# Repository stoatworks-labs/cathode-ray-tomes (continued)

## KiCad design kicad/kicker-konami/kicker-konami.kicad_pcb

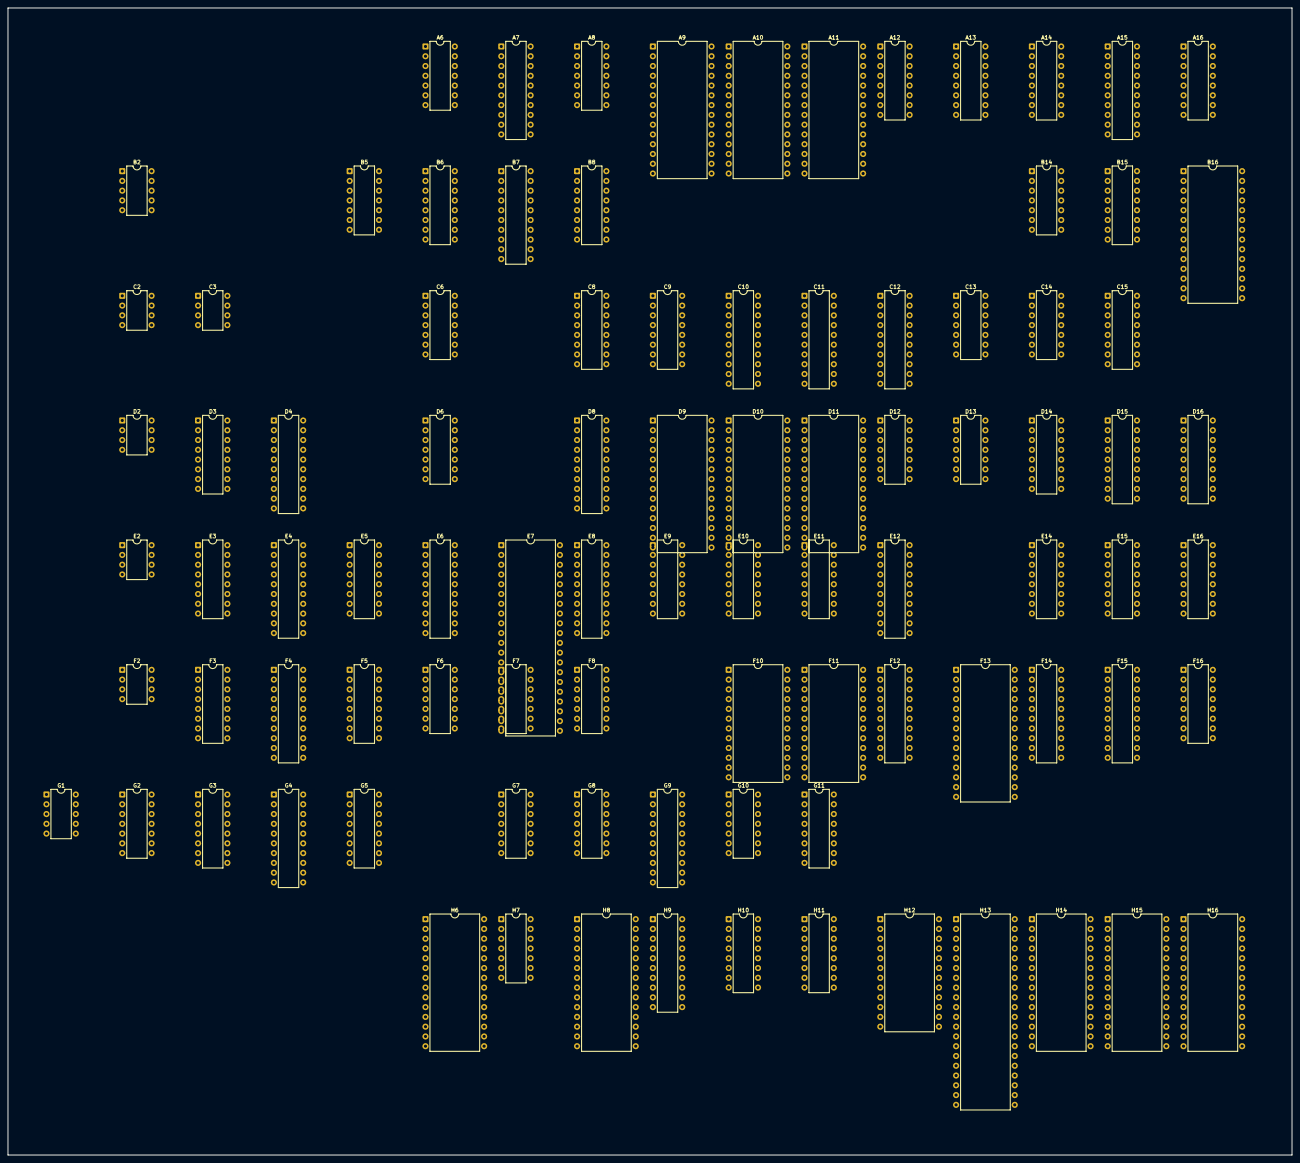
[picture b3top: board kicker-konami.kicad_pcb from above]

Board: 2 copper layers, 333.7 x 298.1 mm, 92 parts (0 on the bottom side), 423 nets, no tracks yet.

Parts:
A6: 74LS32; DIP-14_W7.62mm
A7, A15: 74LS273; DIP-20_W7.62mm
A8: 74LS86; DIP-14_W7.62mm
A9: KICKER_083; DIP-28_W15.24mm
A10, A11: 27128; DIP-28_W15.24mm
A12, A13, A14: TBP24S10N; DIP-16_W7.62mm
A16: 74LS157; DIP-16_W7.62mm
B2: LA4460; DIP-10_W7.62mm
B5: 74LS08; DIP-14_W7.62mm
B6, B15: 74LS174; DIP-16_W7.62mm
B7: 74LS377; DIP-20_W7.62mm
B8: TBP24S10N; DIP-16_W7.62mm
B14: 74LS32; DIP-14_W7.62mm
B16: KICKER_502; DIP-28_W15.24mm
C2, C3: KONAMI_005273; DIP-8_W7.62mm
C6: 74LS74; DIP-14_W7.62mm
C8, C9: 74LS138; DIP-16_W7.62mm
C10, C11: 74LS273; DIP-20_W7.62mm
C12: 74LS245; DIP-20_W7.62mm
C13: 74LS04; DIP-14_W7.62mm
C14: 74LS32; DIP-14_W7.62mm
C15: 74LS139; DIP-16_W7.62mm
D2: KONAMI_005273; DIP-8_W7.62mm
D3: 74LS253; DIP-16_W7.62mm
D4: 74LS273; DIP-20_W7.62mm
D6: 74LS14; DIP-14_W7.62mm
D8: 74LS244; DIP-20_W7.62mm
D9, D10, D11: 27128; DIP-28_W15.24mm
D12: 74LS32; DIP-14_W7.62mm
D13: 74LS08; DIP-14_W7.62mm
D14: 74LS163; DIP-16_W7.62mm
D15, D16: MBM2148; DIP-18_W7.62mm
E2: KONAMI_005273; DIP-8_W7.62mm
E3: 74LS253; DIP-16_W7.62mm
E4: 74LS273; DIP-20_W7.62mm
E5: SN76489AN; DIP-16_W7.62mm
E6, E12: 74LS245; DIP-20_W7.62mm
E7: MC6809E; DIP-40_W15.24mm
E8: 74LS244; DIP-20_W7.62mm
E9, E10, E11: 74LS157; DIP-16_W7.62mm
E14, E15, E16: 74LS163; DIP-16_W7.62mm
F2: KONAMI_005273; DIP-8_W7.62mm
F3: 74LS253; DIP-16_W7.62mm
F4, F15: 74LS273; DIP-20_W7.62mm
F5: SN76489AN; DIP-16_W7.62mm
F6, F7: 74LS74; DIP-14_W7.62mm
F8: 74LS08; DIP-14_W7.62mm
F10, F11: TMM2009P-A; DIP-24_W15.24mm
F12: 74LS245; DIP-20_W7.62mm
F13: KONAMI_085; DIP-28_W15.24mm
F14: 74LS377; DIP-20_W7.62mm
F16: TBP24S10N; DIP-16_W7.62mm
G1: TA7900S; DIP-10_W7.62mm
G2: 74LS07; DIP-14_W7.62mm
G3: 74LS253; DIP-16_W7.62mm
G4: 74LS244; DIP-20_W7.62mm
G5: 74LS367; DIP-16_W7.62mm
G7: 74LS04; DIP-14_W7.62mm
G8, G10: 74LS86; DIP-14_W7.62mm
G9: 74LS273; DIP-20_W7.62mm
G11: 74LS157; DIP-16_W7.62mm
H6: KONAMI_504; DIP-28_W15.24mm
H7: 74LS74; DIP-14_W7.62mm
H8: KONAMI_082; DIP-28_W15.24mm
H9: 74LS244; DIP-20_W7.62mm
H10, H11: 74LS157; DIP-16_W7.62mm
H12: RAM_2016; DIP-24_W15.24mm
H13: KONAMI_503; DIP-40_W15.24mm
H14, H15: 27128; DIP-28_W15.24mm
H16: KICKER_083; DIP-28_W15.24mm

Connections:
+12V: A10.14, A10.20, A10.22, A11.14, A11.20, A11.22, A12.13, A12.14, A13.13, A13.14, A14.13, A14.14, B8.13, B8.14, B14.5, D3.8, D8.1, D8.10, D8.19, D9.14, D9.20, D10.14, D10.20, D11.14, D11.20, D15.9, D15.15, D15.16, D16.9, D16.15, D16.16, E3.8, E6.19, E7.1, E7.39, E8.1, E8.10, E8.19, E9.2, E9.5, E9.11, E9.14, E9.15, E10.15, E11.11, E11.15, F3.8, F7.2, F7.12, F10.12, F11.12, F16.13, F16.14, G1.1, G1.2, G1.5, G3.8, G4.10, G5.15, G8.5, G11.15, H6.14, H8.27, H9.10, H10.14, H10.15, H11.15, H12.18, H13.20, H14.14, H14.20, H14.22, H15.14, H15.20, H15.22
/1P_DOWN: F2.7, F3.5
/1P_LEFT: E2.5, G3.11
/1P_RIGHT: E2.3, G3.5
/1P_SHOOT1: D2.7, E3.11
/1P_SHOOT2: D2.3, E3.5
/1P_START: C2.7, F3.6
/1P_UP: E2.7, F3.11
/2P_LEFT: C2.3, G3.12
/2P_RIGHT: C2.5, G3.4
/2P_SHOOT1: C3.1, E3.12
/2P_SHOOT2: C2.1, E3.4
/2P_START: D2.1, E3.10
/2P_UP: D2.5, F3.12
/A0: D8.11, E7.8
/A1: D8.8, E7.9
/A2: D8.13, E7.10
/A3: D8.6, E7.11
/A4: D8.15, E7.12
/A5: D8.4, E7.13
/A6: D8.17, E7.14
/A7: D8.2, E7.15
/A8: E7.16, E8.2
/A9: E7.17, E8.17
/A10: E7.18, E8.4
/A11: E7.19, E8.6
/A12: E7.20, E8.8
/A13: E7.21, E8.11
/A14: E7.22, E8.13
/A15: E7.23, E8.15
/AD0: D3.14, D8.9, D9.10, D10.10, D11.10, E3.14, E11.3, F3.14, G3.14, H11.3
/AD1: D3.2, D8.12, D9.9, D10.9, D11.9, E3.2, E11.6, F3.2, G3.2, H11.10
/AD2: D8.7, D9.8, D10.8, D11.8, E10.3, H11.6
/AD3: D8.14, D9.7, D10.7, D11.7, E10.13, H11.13
/AD4: D8.5, D9.6, D10.6, D11.6, E10.6, G11.10
/AD5: D8.16, D9.5, D10.5, D11.5, E10.10, G11.6
/AD6: D8.3, D9.4, D10.4, D11.4, E9.6, G11.13
/AD7: D8.18, D9.3, D10.3, D11.3, E9.10, G11.3
/AD8: C9.1, D9.25, D10.25, D11.25, E8.18, E9.3, H10.10
/AD9: C9.2, D9.24, D10.24, D11.24, E8.3, E9.13, H10.6
/AD10: C9.3, D9.21, D10.21, D11.21, E8.16, H10.3
/AD11: C8.1, D9.23, D10.23, D11.23, E8.14
/AD12: C8.2, D9.2, D10.2, D11.2, E8.12
/AD13: C8.3, D9.26, D10.26, D11.26, E8.9
/AD14: C15.13, E8.7
/AD15: C15.14, E8.5
/AFE: C9.14, G2.5
/CHAR0: A9.3, A11.16
/CHAR1: A9.4, A11.11
/CHAR2: A9.5, A10.16
/CHAR3: A9.6, A10.11
/CHAR4: A9.7, A11.17
/CHAR5: A9.8, A11.12
/CHAR6: A9.9, A10.17
/CHAR7: A9.10, A10.12
/CHAR8: A9.25, A11.13
/CHAR9: A9.26, A11.18
/CHAR10: A9.24, A10.18
/CHAR11: A9.20, A10.19
/CHAR12: A9.22, A11.19
/CHAR13: A9.21, A11.15
/CHAR14: A9.23, A10.13
/CHAR15: A9.19, A10.15
/CLK1: B6.9, B16.5, C6.3, G7.8
/CLK2: A9.1, B7.11, F6.3, F6.11, G7.6, G9.11
/CLK2A: A15.11, B14.4, C6.11, F14.11, G7.2, H16.1
/CLK2B: D14.2, D15.10, D16.10, E14.2, E15.2, E16.2, G7.4
/CNTCLR: B16.27, H7.5, H8.1
/COIN1: D4.5, G2.1
/COIN2: D4.15, G2.3
/COIN_1: F2.5, G3.10
/COIN_2: F2.3, G3.6
/COLOR: B15.9, C8.12
/CRA0: A8.8, A10.10, A11.10
/CRA1: A8.6, A10.9, A11.9
/CRA2: A8.11, A10.8, A11.8
/CRA3: A8.3, A10.7, A11.7
/CRA4: A10.6, A11.6, C11.2
/CRA5: A10.5, A11.5, C11.19
/CRA6: A10.4, A11.4, C11.5
/CRA7: A10.3, A11.3, C11.16
/CRA8: A10.25, A11.25, C11.6
/CRA9: A10.24, A11.24, C11.15
/CRA10: A10.21, A11.21, C11.9
/CRA11: A10.23, A11.23, C11.12
/CRA12: A7.9, A10.2, A11.2
/CRA13: A7.15, A10.26, A11.26
/DB0: B15.14, C12.18, D4.18, D9.11, D10.11, D11.11, E4.13, E6.2, E12.11, F4.13, F12.18, F13.1, G3.9, G4.12, G5.9
/DB1: B15.13, C12.17, D4.3, D9.12, D10.12, D11.12, E4.8, E6.3, E12.12, F4.8, F12.17, F13.2, G3.7, G4.9, G5.7
/DB2: B15.3, C12.16, D4.17, D9.13, D10.13, D11.13, E4.14, E6.4, E12.13, F3.9, F4.14, F12.16, F13.3, G4.14, G5.5
/DB3: C12.15, D4.4, D9.15, D10.15, D11.15, E4.7, E6.5, E12.14, F3.7, F4.7, F12.15, F13.4, G4.7, G5.3
/DB4: C12.14, D4.14, D9.18, D10.18, D11.18, E3.9, E4.18, E6.8, E12.17, F4.18, F12.12, F13.5, G4.16
/DB5: C12.13, D4.7, D9.17, D10.17, D11.17, E3.7, E4.3, E6.7, E12.16, F4.3, F12.13, F13.6, G4.5
/DB6: C12.12, D3.9, D4.13, D9.16, D10.16, D11.16, E4.4, E6.6, E12.15, F4.4, F12.14, F13.7, G4.18
/DB7: C12.11, D3.7, D4.8, D9.19, D10.19, D11.19, E4.17, E6.9, E12.18, F4.17, F12.11, F13.8, G4.3
/DV0: C10.3, C11.3, C12.2, H12.9
/DV1: C10.18, C11.18, C12.3, H12.10
/DV2: C10.4, C11.4, C12.4, H12.11
/DV3: C10.17, C11.17, C12.5, H12.13
/DV4: C10.7, C11.7, C12.6, H12.14
/DV5: C10.14, C11.14, C12.7, H12.15
/DV6: C10.8, C11.8, C12.8, H12.16
/DV7: C10.13, C11.13, C12.9, H12.17
/EXTRA1: C3.3, E3.6
/EXTRA2: C3.5, D3.10
/EXTRA3: C3.7, D3.11
/FLIP: C13.3, D4.19, F13.13, G8.4
/H1: B6.13, E5.14, G9.2, H6.10, H7.12
/H2: B6.6, B16.7, D6.5, F5.14, G9.19
/H4: B6.11, C10.11, E11.2, G8.10, G9.5, H10.2
/H8: B6.3, G8.13, G9.16
/H16: E11.5, G9.6, G10.2
/H32: E10.2, F13.9, G9.15, G10.13
/H64: E10.14, F13.12, G9.9, G10.9
/H128: B5.1, G9.12, G10.5
/H256: B6.15, B16.9, E10.11
/HF8: G8.11, H11.2
/HF16: B14.12, G10.8, H11.11
/HF32: B14.13, G10.11, H11.5
/HF64: G10.3, H11.14
/HF128: B14.9, G10.6, G11.11
/HH1: B5.13, B6.12
/HH2: B6.7, H6.11
/HH4: B6.10, G8.1, H6.12, H13.16
/HH8: B6.2, H6.13, H13.17
/HH256: C6.5, F13.16
/IN5: C9.10, G4.1, G4.19
/IN6: C9.9, G5.1
/INTSHOW: C9.13, F13.11
/IOEN: C9.7, D3.1, D3.15, E3.1, E3.15, F3.1, F3.15, G3.1, G3.15
/IOW: A6.5, C9.15
/IRQ: D4.16, F7.10
/LD: A9.27, C13.2, H16.27
/NMI: D4.2, F7.4
/OBJ0: A16.14, B16.18
/OBJ1: A16.3, B16.17
/OBJ2: A16.11, B16.16
/OBJ3: A16.2, B16.15
/OBJCOL0: F16.5, H16.16
/OBJCOL1: F16.6, H16.13
/OBJCOL2: F16.7, H16.17
/OBJCOL3: F16.4, H16.12
/OBJCS1: C8.9, D12.1, D12.4, E12.19
/OBJCS2: C8.10, D12.9, D12.13, F12.19
/OBJNEW0: B16.10, F16.12
/OBJNEW1: B16.11, F16.11
/OBJNEW2: B16.12, F16.10
/OBJNEW3: B16.13, F16.9
/OBJPAL0: F14.16, F16.3
/OBJPAL1: F14.5, F16.2
/OBJPAL2: F14.19, F16.1
/OBJPAL3: F14.2, F16.15
/OD0: E12.9, E15.3, E16.3, F10.9, F15.4
/OD1: E12.8, E15.4, E16.4, F10.10, F15.7
/OD2: E12.7, E15.5, E16.5, F10.11, F15.14
/OD3: E12.6, E15.6, E16.6, F10.13, F15.17
/OD4: D14.3, E12.5, E14.3, F10.14, F15.3
/OD5: D14.4, E12.4, E14.4, F10.15, F15.18
/OD6: D14.5, E12.3, E14.5, F10.16, F15.8
/OD7: D14.6, E12.2, E14.6, F10.17, F15.13
/OR0: E11.4, F10.8, F11.8
/OR1: E11.7, F10.7, F11.7
/OR2: E10.4, F10.6, F11.6
/OR3: E10.12, F10.5, F11.5
/OR4: E10.7, F10.4, F11.4
/OR5: E10.9, F10.3, F11.3
/OR6: E9.7, F10.2, F11.2
/OR7: E9.9, F10.1, F11.1
/OR8: E9.4, F10.23, F11.23
/OR9: E9.12, F10.22, F11.22
/PAL0: A12.5, A13.5, A14.5, A15.6
/PAL1: A12.6, A13.6, A14.6, A15.12
/PAL2: A12.7, A13.7, A14.7, A15.9
/PAL3: A12.4, A13.4, A14.4, A15.15
/PAL4: A12.3, A13.3, A14.3, A15.5
/PAL5: A12.2, A13.2, A14.2, A15.16
/PAL6: A12.1, A13.1, A14.1, A15.19
/PAL7: A12.15, A13.15, A14.15, A15.2
/RC_SERVICE: E2.1, F3.10
/R~WB: C12.1, D6.1, E12.1, F12.1, G5.13, H6.6
/R~W: E6.1, E7.32, G5.14
/R~WBB: D6.2, E11.10, H10.13
/R~WV: A6.4, A6.10, D12.5, D12.10, H6.22
/SCR0: A16.13, B8.12
/SCR1: A16.6, B8.11
/SCR2: A16.10, B8.10
/SCR3: A16.5, B8.9
/SD0: F11.9, F12.2, F14.17, H13.8
/SD1: F11.10, F12.3, F14.4, H13.7
/SD2: F11.11, F12.4, F14.18, H13.6
/SD3: F11.13, F12.5, F14.3, H13.5
/SD4: F11.14, F12.6, H13.4
/SD5: F11.15, F12.7, H13.3
/SD6: F11.16, F12.8, H13.2
/SD7: F11.17, F12.9, H13.1
/SE: C13.9, F6.12, H6.3
/SQ: F6.2, H6.25
/TI1D0: E4.12, E5.10
/TI1D1: E4.9, E5.11
/TI1D2: E4.15, E5.12
/TI1D3: E4.6, E5.13
/TI1D4: E4.19, E5.15
/TI1D5: E4.2, E5.1
/TI1D6: E4.5, E5.2
/TI1D7: E4.16, E5.3
/TI2D0: F4.12, F5.10
/TI2D1: F4.9, F5.11
/TI2D2: F4.15, F5.12
/TI2D3: F4.6, F5.13
/TI2D4: F4.19, F5.15
/TI2D5: F4.2, F5.1
/TI2D6: F4.5, F5.2
/TI2D7: F4.16, F5.3
/TIDATA1: C8.13, E4.11
/TIDATA2: C8.14, F4.11
/TITG1: C9.11, F8.1
/TITG2: C9.12, F8.10
/V1: A7.7, H8.26, H9.2, H13.32
/V2: A7.17, H8.25, H9.17, H13.33
/V4: A7.4, H8.24, H9.4, H13.34
/V8: H8.23, H9.15, H13.35
/V16: F7.3, H8.22, H9.6, H13.36
/V32: H8.21, H9.13, H13.37
/V64: H8.20, H9.8, H13.38
/V128: H8.19, H9.11, H13.39
/VBLANK: F7.11, H8.16
/VD0: H14.16, H16.3
/VD1: H14.11, H16.4
/VD2: H15.16, H16.5
/VD3: H15.11, H16.6
/VD4: H14.17, H16.7
/VD5: H14.12, H16.8
/VD6: H15.17, H16.9
/VD7: H15.12, H16.10
/VD8: H14.18, H16.25
/VD9: H14.13, H16.26
/VD10: H15.18, H16.24
/VD11: H15.13, H16.20
/VD12: H14.19, H16.22
/VD13: H14.15, H16.21
/VD14: H15.19, H16.23
/VD15: H15.15, H16.19
/VGAP: C8.11, F13.15
/VSCR0: F13.27, H9.18
/VSCR1: F13.26, H9.3
/VSCR2: F13.25, H9.16
/VSCR3: F13.24, G11.5, H9.5
/VSCR4: F13.23, G11.14, H9.14
/VSCR5: F13.22, G11.2, H9.7
/VSCR6: F13.21, H9.12, H10.11
/VSCR7: F13.20, H9.9, H10.5
/hflip: A6.1, A7.2, A8.2
/prehflip: A7.3, C10.6
/prevflip: A7.18, C10.15
/tile_pal0: B7.17, C10.2
/tile_pal1: B7.4, C10.19
/tile_pal2: B7.3, C10.5
/tile_pal3: B7.18, C10.16
/vflip: A7.19, A8.5, A8.10, A8.13
/~CLK1: G7.9, H6.26, H7.11
/~COMPBLANK: A16.15, H6.17
/~EE: D6.13, F6.9
/~E: B5.4, C13.8, H7.3
/~H2: C8.6, C9.6, C14.1, D6.6, E9.1, E10.1, E11.1, G11.1, H10.1, H11.1
/~H4: A8.1, G8.8
/~H256B: B5.2, B6.14, C6.9, H6.8
/~H256: C6.12, H8.10
/~HH256: C6.6, H9.1, H9.19
/~IRQ: E7.3, F7.9
/~LDOUT: A7.11, B16.8, C11.11, H6.21
/~LD: A6.2, C13.1, C15.1, H6.20, H13.15
/~NMI: E7.2, F7.5
/~OBJ_SEL: A15.4, A16.1, B16.19
/~Q: B5.5, D6.9, F6.5
/~RESET: D4.1, E7.37, G1.7, H7.1
/~VRAMCS: A6.9, C8.7, C12.19
GND: A12.16, A13.16, A14.16, B8.16, F16.16
unnamed: A7.8, C10.9
unnamed: A7.14, C10.12
unnamed: A7.5, A8.12
unnamed: A7.6, A8.9
unnamed: A7.16, A8.4
unnamed: A9.16, B8.5
unnamed: A9.13, B8.6
unnamed: A9.17, B8.7
unnamed: A9.12, B8.4
unnamed: A9.2, B7.6
unnamed: A15.3, B15.2
unnamed: A15.7, A16.12
unnamed: A15.8, A16.9
unnamed: A15.13, A16.7
unnamed: A15.14, A16.4
unnamed: A15.17, B15.15
unnamed: A15.18, B15.12
unnamed: B5.11, C14.2, D12.2, D12.12
unnamed: B7.7, G8.3
unnamed: B7.2, B8.1
unnamed: B7.5, B8.2
unnamed: B7.16, B8.3
unnamed: B7.19, B8.15
unnamed: A6.3, B7.1
unnamed: B14.10, B14.11
unnamed: B16.1, D16.14
unnamed: B16.2, D16.13
unnamed: B16.3, D16.12
unnamed: B16.4, D16.11
unnamed: B16.26, D15.14
unnamed: B16.25, D15.13
unnamed: B16.24, D15.12
unnamed: B16.23, D15.11
unnamed: B14.6, B16.6
unnamed: B16.22, C13.11, C14.4, C15.3
unnamed: B16.21, C15.2
unnamed: B16.20, C13.5, D13.9
unnamed: C6.2, C6.8
unnamed: C8.15, C9.4, C9.5
unnamed: C13.4, G8.2
unnamed: C13.6, D13.1
unnamed: C13.10, C14.9
unnamed: C14.3, D13.5, D13.13
unnamed: C15.6, E14.1, E15.1
unnamed: C15.7, D14.1, E16.1
unnamed: B5.6, C15.15
unnamed: C8.4, C8.5, C15.12
unnamed: C15.11, D9.22
unnamed: C15.10, D10.22
unnamed: C15.9, D11.22
unnamed: A6.6, D4.11
unnamed: D6.3, G2.6
unnamed: D12.3, D13.12
unnamed: D12.11, D13.4
unnamed: D14.7, D14.10, E16.15
unnamed: D14.14, D16.3
unnamed: D14.13, D16.2
unnamed: D14.12, D16.1
unnamed: D14.11, D16.17
unnamed: C14.6, D14.9, E16.9
unnamed: D15.5, E15.14
unnamed: D15.6, E15.13
unnamed: D15.7, E15.12
unnamed: D15.4, E15.11
unnamed: D15.3, E14.14
unnamed: D15.2, E14.13
unnamed: D15.1, E14.12
unnamed: D15.17, E14.11
unnamed: D13.3, D15.8
unnamed: D16.5, E16.14
unnamed: D16.6, E16.13
unnamed: D16.7, E16.12
unnamed: D16.4, E16.11
unnamed: D13.8, D16.8
unnamed: E5.4, E5.5, F8.2
unnamed: E5.6, F8.3
unnamed: E6.18, E7.31
unnamed: E6.17, E7.30
unnamed: E6.16, E7.29
unnamed: E6.15, E7.28
unnamed: E6.14, E7.27
unnamed: E6.13, E7.26
unnamed: E6.12, E7.25
unnamed: E6.11, E7.24
unnamed: D6.12, E7.34
unnamed: D6.8, E7.35
unnamed: B5.3, E10.5
unnamed: E11.9, F10.20, F11.20
unnamed: E14.7, E14.10, E15.15
unnamed: C14.8, E14.9, E15.9
unnamed: F5.4, F5.5, F8.9
unnamed: F5.6, F8.8
unnamed: D13.11, F10.18
unnamed: D12.6, F10.21
unnamed: D13.6, F11.18
unnamed: D12.8, F11.21
unnamed: B14.8, F13.10
unnamed: F14.7, H13.29
unnamed: F14.8, H13.30
unnamed: D13.2, D13.10, F14.6
unnamed: F14.9, H16.2
unnamed: C14.5, C14.10, F14.1, H13.18
unnamed: F15.11, H13.19
unnamed: F15.2, H14.21, H15.21
unnamed: F15.5, H14.4, H15.4
unnamed: F15.6, H14.3, H15.3
unnamed: F15.9, H14.2, H15.2
unnamed: F15.12, H14.26, H15.26
unnamed: F15.15, H14.25, H15.25
unnamed: F15.16, H14.24, H15.24
unnamed: F15.19, H14.23, H15.23
unnamed: D6.4, G1.9
unnamed: G5.12, H8.17
unnamed: G9.3, H8.2
unnamed: G9.4, H8.4
unnamed: G9.7, H8.6
unnamed: G9.8, H8.8
unnamed: G9.13, H8.9
unnamed: G9.14, H8.7
unnamed: G9.17, H8.5
unnamed: G9.18, H8.3
unnamed: G8.6, G8.9, G8.12, G10.1, G10.4, G10.10, G10.12
unnamed: G11.4, H12.1
unnamed: G11.7, H12.3
unnamed: G11.12, H12.2
unnamed: G11.9, H12.4
unnamed: G7.1, G7.3, G7.5, G7.13, H6.2
unnamed: H6.9, H8.15
unnamed: B5.12, H7.9
unnamed: G7.12, H8.13
unnamed: H10.4, H12.19
unnamed: H10.7, H12.22
unnamed: H10.12, H12.20
unnamed: H10.9, H12.23
unnamed: H11.4, H12.8
unnamed: H11.7, H12.6
unnamed: H11.12, H12.5
unnamed: H11.9, H12.7
unnamed: A6.8, H12.21
unnamed: H13.11, H14.7, H15.7
unnamed: H13.10, H14.6, H15.6
unnamed: H13.14, H14.10, H15.10
unnamed: H13.13, H14.9, H15.9
unnamed: H13.12, H14.8, H15.8
unnamed: H13.9, H14.5, H15.5
VCC: A7.1, A10.1, A10.27, A10.28, A11.1, A11.27, A11.28, A12.8, A13.8, A14.8, A15.1, B6.1, B8.8, B15.1, C6.1, C6.4, C6.10, C6.13, C10.1, C11.1, D3.16, D8.20, D9.1, D9.27, D9.28, D10.1, D10.27, D10.28, D11.1, D11.27, D11.28, D15.18, D16.18, E3.16, E4.1, E7.7, E8.20, E15.7, E15.10, E16.7, E16.10, F3.16, F4.1, F6.1, F6.4, F6.10, F6.13, F7.1, F7.13, F10.19, F10.24, F11.19, F11.24, F15.1, F16.8, G1.4, G3.16, G4.20, G9.1, H6.27, H6.28, H7.2, H7.4, H7.10, H7.13, H8.12, H9.20, H13.40, H14.1, H14.27, H14.28, H15.1, H15.27, H15.28

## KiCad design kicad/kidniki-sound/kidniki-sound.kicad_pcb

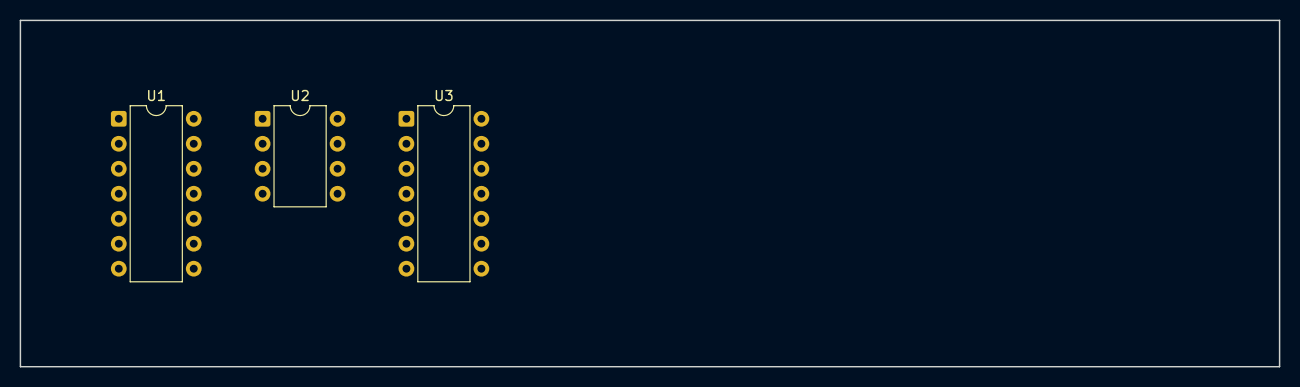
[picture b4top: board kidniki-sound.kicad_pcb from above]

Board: 2 copper layers, 128.0 x 35.2 mm, 3 parts (0 on the bottom side), 6 nets, no tracks yet.

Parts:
U1: LM324; DIP-14_W7.62mm
U2: LM358; DIP-8_W7.62mm
U3: MC14584B; DIP-14_W7.62mm

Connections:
+5V: U1.4, U2.8, U3.14
GND: U1.11, U2.4, U3.7
unnamed: U1.8, U1.9
unnamed: U2.6, U2.7
unnamed: U1.1, U1.2
unnamed: U2.1, U2.2

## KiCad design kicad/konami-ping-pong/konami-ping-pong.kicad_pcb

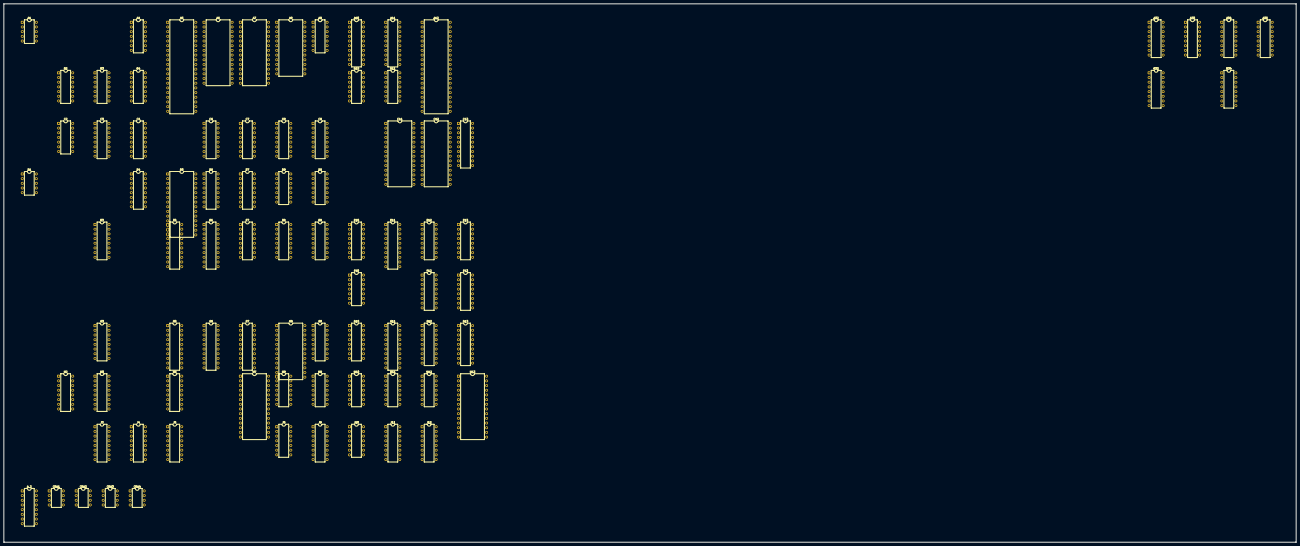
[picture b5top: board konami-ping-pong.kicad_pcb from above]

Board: 2 copper layers, 700.4 x 291.8 mm, 84 parts (0 on the bottom side), 361 nets, no tracks yet.

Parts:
A1: TA7900S; DIP-10_W7.62mm
A4: 74LS74; DIP-14_W7.62mm
A5: Z80CPU; DIP-40_W15.24mm
A6, A7: 27128; DIP-28_W15.24mm
A8: HM6116P-3; DIP-24_W15.24mm
A9: 74LS10; DIP-14_W7.62mm
A10: 74LS245; DIP-20_W7.62mm
A11: 74LS374; DIP-20_W7.62mm
A12: KONAMI_503; DIP-40_W15.24mm
A32, A34: 74LS194; DIP-16_W7.62mm
A33, A35: 74LS157; DIP-16_W7.62mm
A_2: 74LS368; DIP-16_W7.62mm
B2: 74LS07; DIP-14_W7.62mm
B3: 74LS107; DIP-14_W7.62mm
B4: 74xx74; DIP-14_W7.62mm
B10: 7400; DIP-14_W7.62mm
B11: 74xx86; DIP-14_W7.62mm
B32, B34: 74LS194; DIP-16_W7.62mm
C2: 74xx04; DIP-14_W7.62mm
C3: 74LS138; DIP-16_W7.62mm
C4: 74LS174; DIP-16_W7.62mm
C6: 74LS161; DIP-16_W7.62mm
C7, C8, C9: 74LS157; DIP-16_W7.62mm
C11: 27128; DIP-28_W15.24mm
C12: 2764; DIP-28_W15.24mm
C13: 74LS273; DIP-20_W7.62mm
CRA1: 005273X4; DIP-8_W7.62mm
CRA2, CRA3, CRA4: KONAMI_005273; DIP-8_W7.62mm
D1: LA4460; DIP-10_W7.62mm
D4: SN76489AN; DIP-16_W7.62mm
D5: KONAMI_UK; DIP-28_W15.24mm
D6: 74LS161; DIP-16_W7.62mm
D7: 74LS139; DIP-16_W7.62mm
D8: 74LS32; DIP-14_W7.62mm
D9: 74LS00; DIP-14_W7.62mm
E3: 74LS253; DIP-16_W7.62mm
E5, E11: 74LS273; DIP-20_W7.62mm
E6: 74LS245; DIP-20_W7.62mm
E7, E8, E9: 74LS157; DIP-16_W7.62mm
E10: 74LS367; DIP-16_W7.62mm
E12, E13: 74LS163; DIP-16_W7.62mm
F10: 74LS14; DIP-14_W7.62mm
F12, F13: 74LS163; DIP-16_W7.62mm
G3: 74LS253; DIP-16_W7.62mm
G5, G11: 74LS377; DIP-20_W7.62mm
G6, G7: 74LS273; DIP-20_W7.62mm
G8: HM6116P-3; DIP-24_W15.24mm
G9, G10: 74LS161; DIP-16_W7.62mm
G12, G13: MBM2148; DIP-18_W7.62mm
H2, H3: 74LS253; DIP-16_W7.62mm
H5: TBP24S10N; DIP-16_W7.62mm
H7: 2764; DIP-28_W15.24mm
H8, H11: 74LS08; DIP-14_W7.62mm
H9: 74LS74; DIP-14_W7.62mm
H10: 74xx04; DIP-14_W7.62mm
H12: 74LS32; DIP-14_W7.62mm
H13: kicker_502; DIP-28_W15.24mm
J3: TBP18S030; DIP-16_W7.62mm
J4, J9: 74LS174; DIP-16_W7.62mm
J5: 74LS157; DIP-16_W7.62mm
J8: 74LS86; DIP-14_W7.62mm
J10: 74LS74; DIP-14_W7.62mm
J11: TBP24S10N; DIP-16_W7.62mm
J12: 74LS139; DIP-16_W7.62mm

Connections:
/1V: A12.32, G10.7, G10.10, J9.14, J10.9
/2V: A12.33, G10.14, J9.6
/4V: A12.34, G10.13, J9.4
/8V: A12.35, E8.11, G10.12
/16V: A4.11, A12.36, B4.11, E8.5, G10.11
/32V: A9.5, A12.37, E8.14, G9.14
/64V: A9.4, A12.38, E9.14, G9.13
/128V: A9.3, A12.39, E9.2, G9.12
/256V: G9.11, H11.4
/BLANKING: D9.8, J5.15
/CLK6M: A_2.13, D5.11, H13.5
/CPUSEL: C2.2, C7.1, C8.1, C9.1, E7.1, E8.1, E9.1, H8.10
/DB0: A10.11, C4.11, D5.8, E5.14, E6.14, H2.9
/DB1: A10.12, C4.13, D5.7, E5.7, E6.13, H2.7
/DB2: A10.13, C4.4, D5.6, E5.4, E6.16, H3.9
/DB3: A10.14, C4.6, D5.5, E5.17, E6.15, H3.7
/DB4: A10.15, C4.3, D5.4, E3.9, E5.3, E6.18
/DB5: A10.16, C4.14, D5.3, E3.7, E5.18, E6.17
/DB6: A10.17, D5.2, E5.8, E6.11, G3.9
/DB7: A10.18, D5.1, E5.13, E6.12, G3.7
/H1: A4.5, A9.1, A_2.12, B10.1, C6.7, C6.10, D4.14, D5.10
/H2: A9.13, B10.2, C6.14, H13.7
/H4: A9.2, B11.1, C2.13, C6.13, E9.5, G6.11, J8.13
/H4': A12.16, B11.6, C7.5, J12.2
/H8: A12.17, B11.13, C6.12, C7.14, E7.2
/H8'': A11.1, H10.10
/H8´: B11.8, J12.3
/H16: C6.11, C7.2, E7.11, J10.3
/H32: C7.11, D6.14, D9.12, E7.5
/H64: C8.5, D6.13, E7.14, F10.1
/H128: D6.12, E8.2, H8.12
/H256: D6.11, H8.13, H10.5, H12.1
/H256´: H9.12, H12.3, H13.9
/LD_A: A33.6, A33.11, A35.6, A35.11, D9.4, H10.12
/MAINA0: A5.30, A6.10, A7.10, C7.6, E7.3
/MAINA1: A5.31, A6.9, A7.9, C7.13, E7.10
/MAINA2: A5.32, A6.8, A7.8, C7.3, E7.6
/MAINA3: A5.33, A6.7, A7.7, C7.10, E7.13
/MAINA4: A5.34, A6.6, A7.6, C8.6, E8.3
/MAINA5: A5.35, A6.5, A7.5, C8.13, E8.10
/MAINA6: A5.36, A6.4, A7.4, C8.3, E8.6
/MAINA7: A5.37, A6.3, A7.3, C8.10, E8.13, E10.14
/MAINA8: A5.38, A6.25, A7.25, C9.10, E9.13, E10.12
/MAINA9: A5.39, A6.24, A7.24, C3.1, C9.6, E9.3
/MAINA10: A5.40, A6.21, A7.21, C3.2, C9.3, E9.6
/MAINAB7: E3.14, E10.13, G3.14, H2.14, H3.14
/MAINAB8: E3.2, E10.11, G3.2, H2.2, H3.2
/MAIN_DCDR: D7.10, D8.4, H10.3
/OC0: H13.18, J5.2
/OC1: H13.17, J5.5
/OC2: H13.16, J5.11
/OC3: H13.15, J5.14
/PEH: C2.3, D6.15
/PXL_CLK: A32.11, A34.11, B32.11, B34.11, C2.6, G5.11, G11.11, J4.9
/PXL_CLK': A4.3, C2.8, C6.2, D6.2
/PXL_CLK'': C2.10, E12.2, E13.2, F12.2, F13.2, G12.10, G13.10, H12.4
/RH: C8.14, H8.11
/VRAM_~CE: D7.4, D8.1, E6.19
/VRAM_~CS: G8.18, H8.8
/VRAM_~WE: D8.3, E6.1, G8.21
/connectors/RC_1BTN1: CRA1.7, H2.5
/connectors/RC_1BTN2: CRA3.3, E3.11
/connectors/RC_1DOWN: CRA4.1, H3.5
/connectors/RC_1LEFT: CRA2.1, G3.5
/connectors/RC_1RIGHT: CRA2.3, G3.11
/connectors/RC_1START: CRA3.7, E3.10
/connectors/RC_1UP: CRA3.1, E3.5
/connectors/RC_2DOWN: CRA4.7, H2.11
/connectors/RC_2START: CRA4.5, H3.6
/connectors/RC_2UP: CRA4.3, H3.11
/connectors/RC_COIN1: CRA2.5, G3.6
/connectors/RC_COIN2: CRA2.7, G3.10
/connectors/RC_SERVICE: CRA3.5, E3.6
/gfx/A0: E7.4, G8.8
/gfx/A1: E7.9, G8.7
/gfx/A2: E7.7, G8.6
/gfx/A3: E7.12, G8.5
/gfx/A4: E8.4, G8.4
/gfx/A5: E8.9, G8.3
/gfx/A6: E8.7, G8.2
/gfx/A7: E8.12, G8.1
/gfx/A8: E9.12, G8.23
/gfx/A9: E9.4, G8.22
/gfx/A10: E9.7, G8.19
/gfx/CHA0: H7.10, J8.3
/gfx/CHA1: H7.9, J8.8
/gfx/CHA2: H7.8, J8.6
/gfx/CHA3: H7.7, J8.11
/gfx/CHA4: G7.16, H7.6
/gfx/CHA5: G7.15, H7.5
/gfx/CHA6: G7.12, H7.4
/gfx/CHA7: G7.9, H7.3
/gfx/CHA8: G7.6, H7.25
/gfx/CHA9: G7.5, H7.24
/gfx/CHA10: G7.2, H7.21
/gfx/CHA11: G7.19, H7.23
/gfx/CHA12: H7.2, J9.2
/gfx/CHPAL0: G5.2, H5.7
/gfx/CHPAL1: G5.5, H5.4
/gfx/CHPAL2: G5.12, H5.3
/gfx/CHPAL3: G5.9, H5.2
/gfx/CHPAL4: G5.6, H5.1
/gfx/COL0: A33.4, H5.5
/gfx/COL1: A33.12, H5.6
/gfx/COLA0: J3.10, J4.12
/gfx/COLA1: J3.11, J4.10
/gfx/COLA2: J3.12, J4.7
/gfx/COLA3: J3.13, J4.15
/gfx/D0: E6.6, G6.17, G7.17, G8.9
/gfx/D1: E6.7, G6.14, G7.14, G8.10
/gfx/D2: E6.4, G6.13, G7.13, G8.11
/gfx/D3: E6.5, G6.8, G7.8, G8.13
/gfx/D4: E6.2, G6.7, G7.7, G8.14
/gfx/D5: E6.3, G6.4, G7.4, G8.15
/gfx/D6: E6.9, G6.3, G7.3, G8.16
/gfx/D7: E6.8, G6.18, G7.18, G8.17
/gfx/HFLIP: G5.18, J8.12, J9.12
/gfx/HFLIPQ: A33.1, G5.19
/gfx/PLANEA0: B32.3, H7.16
/gfx/PLANEA1: B32.4, H7.17
/gfx/PLANEA2: B32.5, H7.18
/gfx/PLANEA3: B32.6, H7.19
/gfx/PLANEB0: A32.3, H7.11
/gfx/PLANEB1: A32.4, H7.12
/gfx/PLANEB2: A32.5, H7.13
/gfx/PLANEB3: A32.6, H7.15
/gfx/PRE-HFLIP: G6.2, J9.13
/gfx/PRE-VFLIP: G6.19, J9.11
/gfx/PXL0: J4.13, J5.4
/gfx/PXL1: J4.11, J5.7
/gfx/PXL2: J4.6, J5.9
/gfx/PXL3: J4.14, J5.12
/gfx/VFLIP: J8.2, J8.5, J8.10, J9.10
/gfx/pwb400322_gfx/A0: A32.15, A33.2
/gfx/pwb400322_gfx/A3: A32.12, A33.3
/gfx/pwb400322_gfx/B0: A33.14, B32.15
/gfx/pwb400322_gfx/B3: A33.13, B32.12
/gfx/pwb400322_gfx/S0: A32.9, A33.9, B32.9
/gfx/pwb400322_gfx/S1: A32.10, A33.7, B32.10
/gfx/~OSELQ: J3.14, J4.2
/hvcounter/CPX: G9.2, G10.2, J10.6, J10.11
/hvcounter/VSS: B11.2, B11.5, B11.9, B11.12, C6.3, C6.4, C6.5, C6.6, D6.3, D6.4, D6.6, G9.6, G10.3, G10.4
/hvcounter/~224V: A4.12, A9.6
/hvcounter/~HS: H11.5, J10.5
/hvcounter/~VB: A4.9, D9.10
/main/BASE_CLK: A_2.9, B3.9, B3.12
/main/CPU_CLK: A5.6, A_2.11
/main/D0: A5.14, A6.11, A7.11, D5.20
/main/D1: A5.15, A6.12, A7.12, D5.21
/main/D2: A5.12, A6.13, A7.13, D5.22
/main/D3: A5.8, A6.15, A7.15, D5.23
/main/D4: A5.7, A6.16, A7.16, D5.24
/main/D5: A5.9, A6.17, A7.17, D5.25
/main/D6: A5.10, A6.18, A7.18, D5.26
/main/D7: A5.13, A6.19, A7.19, D5.27
/main/MAINA11: A5.1, A6.23, A7.23, H8.9
/main/MAINA12: A5.2, A6.2, A7.2, D7.2
/main/MAINA13: A5.3, A6.26, A7.26, C3.6, D7.3
/main/MAINA14: A5.4, D8.5, D9.1
/main/MAINA15: A5.5, D7.14
/main/Q: B3.3, B3.8
/main/RAW_CLK: B3.5, C2.5, C2.9, C2.11
/main/ROM0_~CS: A7.22, D8.6
/main/ROM1_~CS: A6.22, D9.3
/main/VSS: A1.1, A1.2, A1.5, A5.29, A6.14, A6.20, A7.14, A7.20, A_2.1, A_2.15, B4.2, B4.12, D5.14
/main/~CPUSEL: C2.1, D5.9
/main/~EXT: C3.4, C3.5, D5.18, D7.1
/main/~INT: A5.16, B4.5
/main/~IO_WR: C3.15, C4.9
/main/~IRQCLR: B4.4, C4.5
/main/~MREQ: A5.19, D7.15
/main/~NMICLR: B4.10, C4.7
/main/~NMI: A5.17, B4.9
/main/~Q: B3.1, B3.6
/main/~RFSH: A5.28, D7.13
/main/~WAIT: A5.24, D5.19
/main/~WRB: C3.3, D5.17, D8.2, D8.13
/object/AA0: A8.8, C7.7
/object/AA1: A8.7, C7.12
/object/AA2: A8.6, C7.4
/object/AA3: A8.5, C7.9
/object/AA4: A8.4, C8.7
/object/AA5: A8.3, C8.12
/object/AA6: A8.2, C8.4
/object/AA7: A8.1, C8.9
/object/AA8: A8.23, C9.9
/object/AA9: A8.22, C9.7
/object/AA10: A8.19, C9.4
/object/ATTR0: E11.19, G11.13
/object/ATTR1: E11.2, G11.14
/object/ATTR2: E11.16, G11.17
/object/ATTR3: E11.5, G11.18
/object/ATTR4: E11.15, G11.7
/object/ATTR5: E11.6, H9.2
/object/ATTR6: E10.6, E11.12
/object/ATTR7: E10.10, E11.9
/object/COL0: A35.4, J11.5
/object/COL1: A35.12, J11.6
/object/DA0: A8.9, A10.9, A11.13, C13.14, E11.18, E12.3, E13.3
/object/DA1: A8.10, A10.8, A11.8, C13.17, E11.3, E12.4, E13.4
/object/DA2: A8.11, A10.7, A11.14, C13.4, E11.17, E12.5, E13.5
/object/DA3: A8.13, A10.6, A11.7, C13.7, E11.4, E12.6, E13.6
/object/DA4: A8.14, A10.5, A11.17, C13.8, E11.14, F12.3, F13.3
/object/DA5: A8.15, A10.4, A11.4, C13.13, E11.7, F12.4, F13.4
/object/DA6: A8.16, A10.3, A11.18, C13.3, E11.13, F12.5, F13.5
/object/DA7: A8.17, A10.2, A11.3, C13.18, E11.8, F12.6, F13.6
/object/DN0: A11.12, A12.8
/object/DN1: A11.9, A12.7
/object/DN2: A11.15, A12.6
/object/DN3: A11.6, A12.5
/object/DN4: A11.16, A12.4
/object/DN5: A11.5, A12.3
/object/DN6: A11.19, A12.2, E10.7
/object/DN7: A11.2, A12.1, E10.9
/object/HFLIP: A12.30, G11.4
/object/HFLIP': A35.1, G11.5
/object/IC0: H13.10, J11.9
/object/IC1: H13.11, J11.10
/object/IC2: H13.12, J11.11
/object/IC3: H13.13, J11.12
/object/OBJ0: A12.14, C11.10, C12.10
/object/OBJ1: A12.13, C11.9, C12.9
/object/OBJ2: A12.12, C11.8, C12.8
/object/OBJ3: A12.11, C11.7, C12.7
/object/OBJ4: A12.10, C11.6, C12.6
/object/OBJ5: A12.9, C11.5, C12.5
/object/OBJ6: C11.4, C12.4, C13.15
/object/OBJ7: C11.3, C12.3, C13.16
/object/OBJ8: C11.25, C12.25, C13.5
/object/OBJ9: C11.24, C12.24, C13.6
/object/OBJ10: C11.21, C12.21, C13.9
/object/OBJ11: C11.23, C12.23, C13.12
/object/OBJ12: C11.2, C12.2, C13.2
/object/OBJ13: C11.26, C13.19
/object/OBJD0: B34.3, C11.11, C12.11
/object/OBJD1: B34.4, C11.12, C12.12
/object/OBJD2: B34.5, C11.13, C12.13
/object/OBJD3: B34.6, C11.15, C12.15
/object/OBJD4: A34.3, C11.16, C12.16
/object/OBJD5: A34.4, C11.17, C12.17
/object/OBJD6: A34.5, C11.18, C12.18
/object/OBJD7: A34.6, C11.19, C12.19
/object/PAL0: G11.12, J11.7
/object/PAL1: G11.15, J11.4
/object/PAL2: G11.16, J11.3
/object/PAL3: G11.19, J11.2
/object/PAL4: G11.6, J11.1
/object/linebuffer/A0: E13.14, G13.5
/object/linebuffer/A1: E13.13, G13.6
/object/linebuffer/A2: E13.12, G13.7
/object/linebuffer/A3: E13.11, G13.4
/object/linebuffer/A4: F13.14, G13.3
/object/linebuffer/A5: F13.13, G13.2
/object/linebuffer/A6: F13.12, G13.1
/object/linebuffer/A7: F13.11, G13.17
/object/linebuffer/AA0: E12.14, G12.5
/object/linebuffer/AA1: E12.13, G12.6
/object/linebuffer/AA2: E12.12, G12.7
/object/linebuffer/AA3: E12.11, G12.4
/object/linebuffer/AA4: F12.14, G12.3
/object/linebuffer/AA5: F12.13, G12.2
/object/linebuffer/AA6: F12.12, G12.1
/object/linebuffer/AA7: F12.11, G12.17
/object/linebuffer/AD0: G12.11, H13.1
/object/linebuffer/AD1: G12.12, H13.2
/object/linebuffer/AD2: G12.13, H13.3
/object/linebuffer/AD3: G12.14, H13.4
/object/linebuffer/BD0: G13.11, H13.25
/object/linebuffer/BD1: G13.12, H13.26
/object/linebuffer/BD2: G13.13, H13.24
/object/linebuffer/BD3: G13.14, H13.23
/object/linebuffer/LD: H10.9, H12.9, H13.22, J12.13
/object/linebuffer/LINEA: G12.8, H11.3
/object/linebuffer/LINEB: G13.8, H11.11
/object/linebuffer/VSS: G12.15, G12.16, G13.15, G13.16, H12.2, H12.5
/object/linebuffer/~LDD: H10.1, H11.1, H13.20
/object/linebuffer/~MRA: E12.1, F12.1, J12.11
/object/linebuffer/~MRB: E13.1, F13.1, J12.10
/object/linebuffer/~PEA: E12.9, F12.9, H12.8
/object/linebuffer/~PEB: E13.9, F13.9, H12.11
/object/pwb400322/A0: A34.15, A35.2
/object/pwb400322/A3: A34.12, A35.3
/object/pwb400322/B0: A35.14, B34.15
/object/pwb400322/B3: A35.13, B34.12
/object/pwb400322/S0: A34.9, A35.9, B34.9
/object/pwb400322/S1: A34.10, A35.7, B34.10
/object/~LINECS: G11.2, H11.2, H11.13
/object/~OBJDATA: A12.19, C13.11, H9.3
/object/~OEB: A8.20, C9.12
/object/~OE_M: C12.22, H9.6
/object/~OE_OF: C11.22, H9.5
/object/~PRE_LINE: A12.29, G11.3
/sound/SND0: D4.10, E5.15
/sound/SND1: D4.11, E5.6
/sound/SND2: D4.12, E5.5
/sound/SND3: D4.13, E5.16
/sound/SND4: D4.15, E5.2
/sound/SND5: D4.1, E5.19
/sound/SND6: D4.2, E5.9
/sound/SND7: D4.3, E5.12
/sound/VSS: D1.3, D1.8
/~H4: C2.12, D9.5
/~H8´: A11.11, E10.1, H10.11, J12.4
/~H15: E11.11, J12.7
/~H256: C8.2, H10.6, J10.4
/~HB: D9.9, H9.9
/~INT_CK: A4.8, B4.3
/~IO_EN: C3.11, E3.1, E3.15, G3.1, G3.15, H2.1, H2.15, H3.1, H3.15
/~LDOUT: A9.12, G7.11, H13.8, J9.9
/~LD: A12.15, B10.3, H10.13, J12.1, J12.15
/~MAIN_DCDR: D9.2, H10.4
/~OBJCOL: A12.18, G11.1, H9.11, H12.10, H12.12
/~OBJ_WE: A8.21, A10.1, D8.11
/~ORAM_CS: A10.19, D7.5, D8.12
/~OSEL: H13.19, J4.3, J5.1
/~PEH: C2.4, D6.9
/~RD: A5.21, C9.13, D5.13
/~RESET: A1.7, A5.26, C4.1, H13.27
/~SND_CMD: C3.13, H8.2
/~SND_LATCH: C3.14, E5.11
GND: A1.4, A4.1, A4.4, A4.10, A4.13, A5.11, A6.1, A6.27, A6.28, A7.1, A7.27, A7.28, A8.24, A12.40, A32.1, A33.5, A33.10, A34.1, A35.5, A35.10, B3.4, B3.10, B3.11, B3.13, B4.1, B4.7, B4.13, B4.14, B11.7, B11.14, B32.1, B34.1, C2.7, C2.14, C6.1, C6.9, C11.1, C11.27, C11.28, C12.1, C12.27, C12.28, C13.1, D5.28, D6.1, D6.5, E3.8, E3.16, E11.1, E12.7, E12.10, E13.7, E13.10, G3.8, G3.16, G6.1, G7.1, G8.24, G9.1, G9.3, G9.4, G9.5, G10.1, G10.5, G10.6, G12.9, G12.18, G13.9, G13.18, H2.8, H2.16, H3.8, H3.16, H5.8, H5.16, H7.1, H7.27, H7.28, H9.1, H9.4, H9.10, H9.13, H10.7, H10.14, J9.1, J10.1, J10.10, J10.13, J11.8, J11.16
unnamed: A1.9, F10.4
unnamed: A4.2, A4.6
unnamed: A_2.14, B3.2
unnamed: B2.12, F10.3
unnamed: B11.3, B11.4
unnamed: B11.10, B11.11
unnamed: B2.13, C3.12
unnamed: B2.3, C4.10
unnamed: B2.5, C4.12
unnamed: C6.15, D6.7, D6.10
unnamed: D4.4, D4.5, H8.1
unnamed: D4.6, H8.3
unnamed: D5.12, D7.9
unnamed: D9.13, F10.2
unnamed: E12.15, F12.7, F12.10
unnamed: E13.15, F13.7, F13.10
unnamed: G5.3, G6.16
unnamed: G5.4, G6.15
unnamed: G5.7, G6.6
unnamed: G5.8, G6.9
unnamed: G5.13, G6.12
unnamed: D9.6, G5.1
unnamed: G6.5, J9.3
unnamed: F10.5, G9.15
unnamed: G9.7, G9.10, G10.15
unnamed: F10.6, G9.9, G10.9
unnamed: H5.12, J5.3
unnamed: H5.11, J5.6
unnamed: H5.10, J5.10
unnamed: H5.9, J5.13
unnamed: H10.2, H11.12
unnamed: H10.8, H12.13
unnamed: H12.6, H13.6
unnamed: H13.21, J12.14
unnamed: J8.4, J9.5
unnamed: J8.9, J9.7
unnamed: J8.1, J9.15
unnamed: D9.11, J10.2
unnamed: J10.8, J10.12
VSS: A8.12, A8.18, A12.20, A33.15, A35.15, C7.15, C8.11, C8.15, C9.2, C9.5, C9.11, C9.14, C9.15, C11.14, C11.20, C12.14, C12.20, E7.15, E8.15, E9.15, E10.15, G8.12, G8.20, H5.13, H5.14, H5.15, H7.14, H7.20, H7.22, J3.15, J4.1, J11.13, J11.14, J11.15
